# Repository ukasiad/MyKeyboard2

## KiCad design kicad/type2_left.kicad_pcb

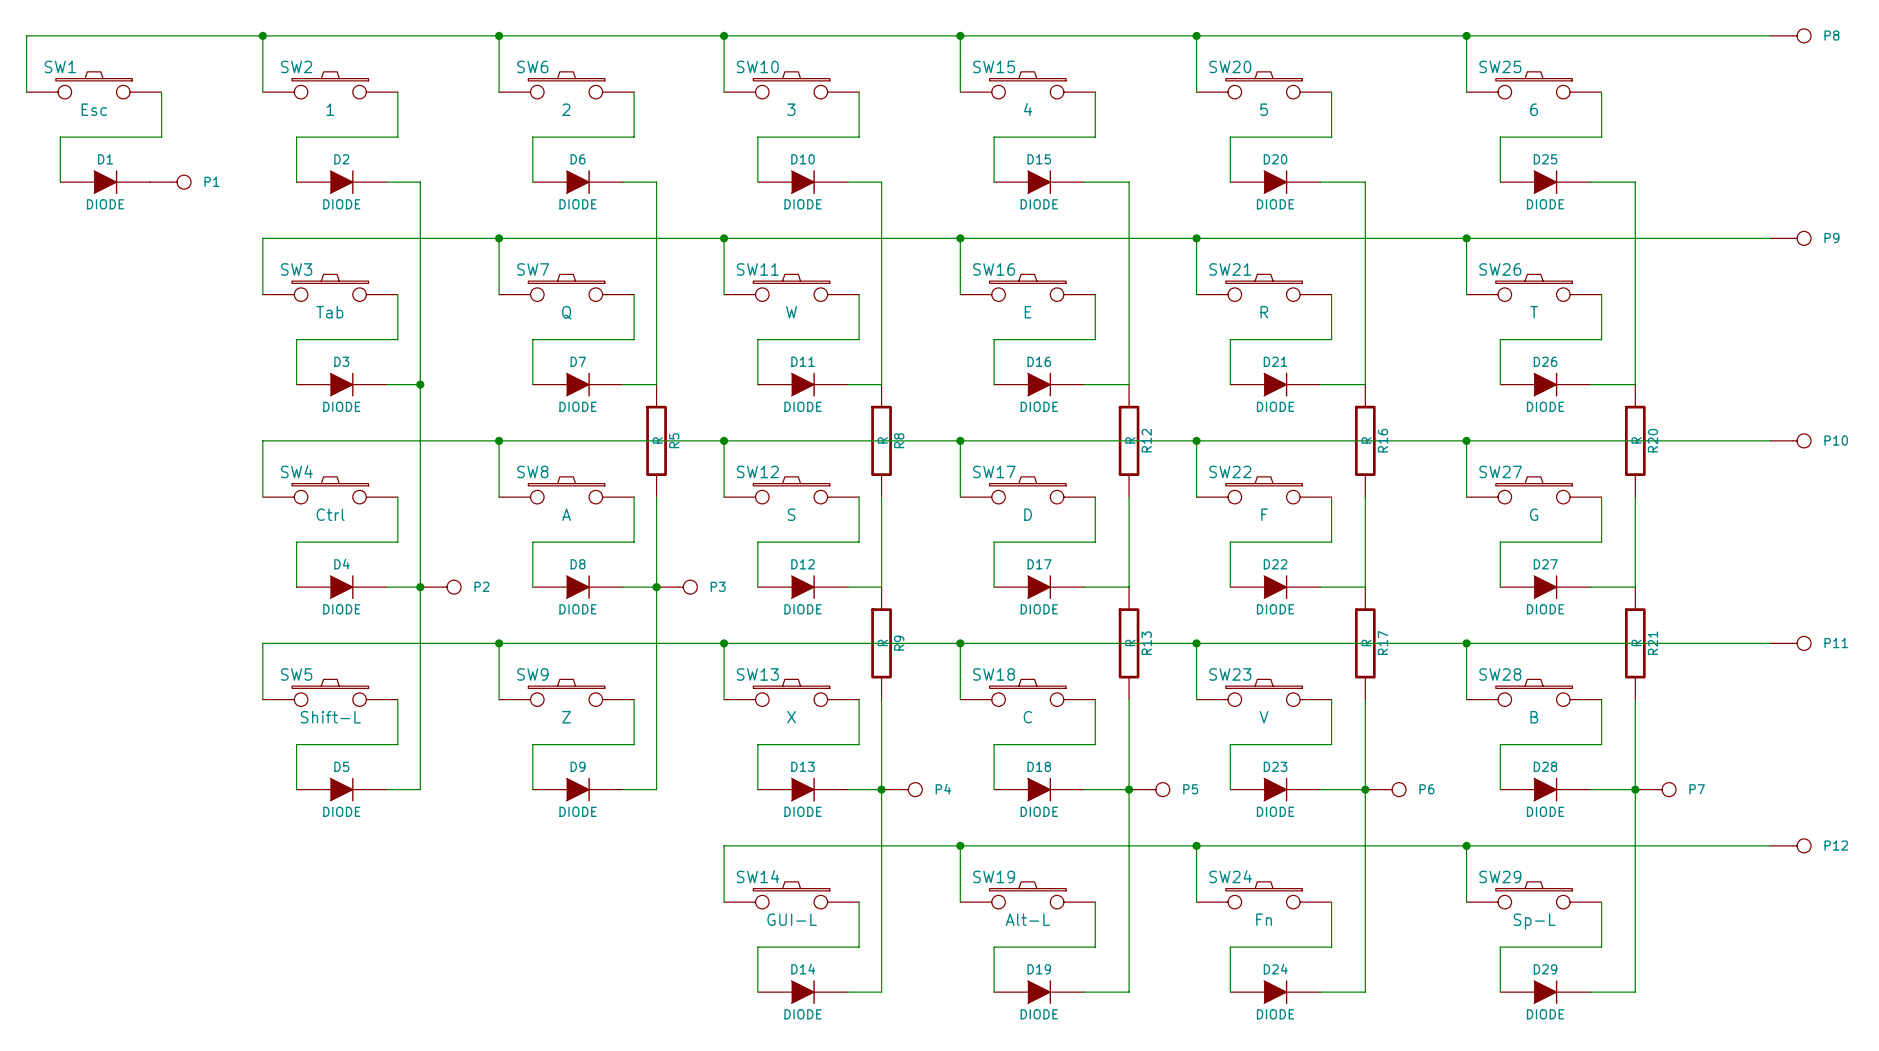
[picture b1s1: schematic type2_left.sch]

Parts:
D1, D2, D3, D4, D5, D6, D7, D8, D9, D10, D11, D12, D13, D14, D15, D16, D17, D18, D19, D20, D21, D22, D23, D24, D25, D26, D27, D28, D29: DIODE
P1, P2, P3, P4, P5, P6, P7, P8, P9, P10, P11, P12: CONN_1
R5, R8, R9, R12, R13, R16, R17, R20, R21: R
SW1: Esc
SW2: 1
SW3: Tab
SW4: Ctrl
SW5: Shift-L
SW6: 2
SW7: Q
SW8: A
SW9: Z
SW10: 3
SW11: W
SW12: S
SW13: X
SW14: GUI-L
SW15: 4
SW16: E
SW17: D
SW18: C
SW19: Alt-L
SW20: 5
SW21: R
SW22: F
SW23: V
SW24: Fn
SW25: 6
SW26: T
SW27: G
SW28: B
SW29: Sp-L

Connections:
unnamed: D1.1 (A), SW1.1
unnamed: D8.1 (A), SW8.1
unnamed: D6.2 (K), D7.2 (K), R5.1
unnamed: D7.1 (A), SW7.1
unnamed: D2.1 (A), SW2.1
unnamed: D6.1 (A), SW6.1
unnamed: D5.1 (A), SW5.1
unnamed: D2.2 (K), D3.2 (K), D4.2 (K), D5.2 (K), P2.1
unnamed: D10.2 (K), D11.2 (K), R8.1
unnamed: D13.1 (A), SW13.1
unnamed: D12.1 (A), SW12.1
unnamed: D11.1 (A), SW11.1
unnamed: D12.2 (K), R8.2, R9.1
unnamed: D4.1 (A), SW4.1
unnamed: D10.1 (A), SW10.1
unnamed: D9.1 (A), SW9.1
unnamed: D8.2 (K), D9.2 (K), P3.1, R5.2
unnamed: P12.1, SW14.2, SW19.2, SW24.2, SW29.2
unnamed: D3.1 (A), SW3.1
unnamed: D23.1 (A), SW23.1
unnamed: D25.2 (K), D26.2 (K), R20.1
unnamed: D26.1 (A), SW26.1
unnamed: D25.1 (A), SW25.1
unnamed: D23.2 (K), D24.2 (K), P6.1, R17.2
unnamed: D27.2 (K), R20.2, R21.1
unnamed: D24.1 (A), SW24.1
unnamed: D22.2 (K), R16.2, R17.1
unnamed: D22.1 (A), SW22.1
unnamed: D29.1 (A), SW29.1
unnamed: D13.2 (K), D14.2 (K), P4.1, R9.2
unnamed: D28.2 (K), D29.2 (K), P7.1, R21.2
unnamed: D28.1 (A), SW28.1
unnamed: D27.1 (A), SW27.1
unnamed: D15.1 (A), SW15.1
unnamed: D18.1 (A), SW18.1
unnamed: D17.1 (A), SW17.1
unnamed: D16.1 (A), SW16.1
unnamed: D14.1 (A), SW14.1
unnamed: D18.2 (K), D19.2 (K), P5.1, R13.2
unnamed: D20.2 (K), D21.2 (K), R16.1
unnamed: D21.1 (A), SW21.1
unnamed: D20.1 (A), SW20.1
unnamed: D17.2 (K), R12.2, R13.1
unnamed: D15.2 (K), D16.2 (K), R12.1
unnamed: D19.1 (A), SW19.1
unnamed: P11.1, SW5.2, SW9.2, SW13.2, SW18.2, SW23.2, SW28.2
unnamed: P10.1, SW4.2, SW8.2, SW12.2, SW17.2, SW22.2, SW27.2
unnamed: P8.1, SW1.2, SW2.2, SW6.2, SW10.2, SW15.2, SW20.2, SW25.2
unnamed: P9.1, SW3.2, SW7.2, SW11.2, SW16.2, SW21.2, SW26.2
unnamed: D1.2 (K), P1.1

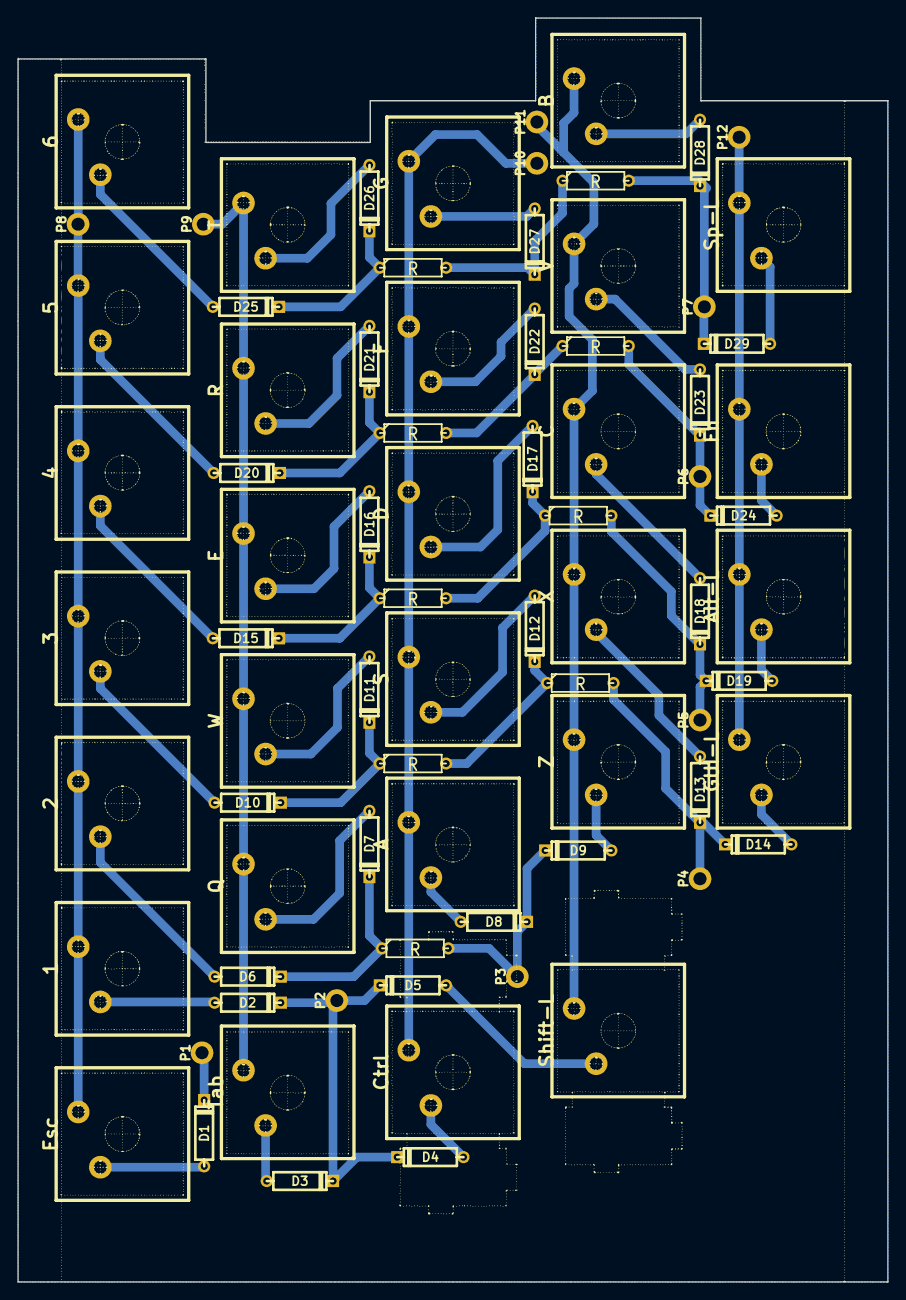
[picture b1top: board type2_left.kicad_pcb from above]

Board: 2 copper layers, 100.0 x 145.3 mm, 79 parts (0 on the bottom side), 50 nets.

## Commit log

2014-10-28 ブログ公開用に新規作成。
2014-10-28 無視ファイル調整
2014-10-28 不要ファイル削除
